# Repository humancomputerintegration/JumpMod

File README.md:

# JumpMod: Haptic Backpack that Modifies Users’ Perceived Jump

This is the repository for PCB schematics, Arduino code and hardware design files used to build the haptic backpack the "JumpMod: Haptic Backpack that Modifies Users’ Perceived Jump" paper (ACM CHI2023) by Romain Nith, Jacob Serfaty, Samuel Shatzkin, Alan Shen, and Pedro Lopes.

For more information, please refer to our paper: http://lab.plopes.org/#JumpMod

# parts for each assembly

| **Item**                                      | **Qty** | **Exemplary link**                                                                                                                                                                                                                                        | **Approx. unit cost (in USD)** |
| --------------------------------------------- | ------- | --------------------------------------------------------------------------------------------------------------------------------------------------------------------------------------------------------------------------------------------------------- | ------------------------------ |
| **Mechanical Frame**                          |
| 400mm extrusion aluminum                      | 2       | [Amazon link](https://www.amazon.com/gp/product/B08Y8N7FD1/ref=ppx_yo_dt_b_search_asin_title?ie=UTF8&psc=1)                                                                                                                                               | 4.75                           |
| 480mm extrusion aluminum                      | 1       | [Amazon link](https://www.amazon.com/Coavoo-Aluminum-Extrusion-Extruded-Profiles/dp/B0B4J6D1R6/ref=sr_1_4?crid=1TWB9FE1O3XJL&keywords=480mm+T+Slot+2020+Aluminum&qid=1670883696&s=industrial&sprefix=480mm+t+slot+2020+aluminum%2Cindustrial%2C94&sr=1-4) | 10.99                          |
| Extrusion aluminum corner bracket             | 8       | [Amazon link](https://a.co/d/40E8cxs)                                                                                                                                               | 1.10                           |
| M6 screws and nuts                            | 25      | [Amazon link](https://a.co/d/0i1jSaT)                                                                                                                                               | 1.10                           |
| Meister Backpack Straps                       | 1       | [Amazon link](https://www.amazon.com/gp/product/B077MZQ57Y/ref=ppx_yo_dt_b_search_asin_title?ie=UTF8&psc=1)                                                                                                                                               | 19.99                          |
| Hip straps                                    | 2       | [Amazon link](https://www.amazon.com/Lashing-Adjustable-Tie-Down-Motorcycle-Luggage/dp/B07JRG7LJV/ref=sr_1_8?keywords=tie+down+strap&qid=1641501015&sprefix=tie+down+str,aps,84&sr=8-8&th=1)                                                              | 5.00                           |
| Back support                                  | 2       | 3D printed                                                                                                                                                                                                                                                |                                |
| **Belt system**                               |
| 2GT-6 Timing Belt with Steel Core             | 1       | [Amazon link](https://www.amazon.com/gp/product/B07BDG8B1S/ref=ox_sc_act_title_3?smid=A2TMCEJ2C8SAEN&psc=1)                                                                                                                                               | 9.65                           |
| MGN12H 400mm Linear Rail                      | 1       | [Amazon link](https://www.amazon.com/gp/product/B07SL1HHSS/ref=ppx_yo_dt_b_search_asin_title?ie=UTF8&psc=1)                                                                                                                                               | 25.99                          |
| Micro limit switch                            | 2       | [Amazon link](https://www.amazon.com/gp/product/B07X142VGC/ref=ppx_yo_dt_b_search_asin_title?ie=UTF8&psc=1)                                                                                                                                               | 0.59                           |
| Rail limiter                                  | 2       | 3D printed                                                                                                                                                                                                                                                |                                |
| Tension system mount                          | 1       | 3D printed                                                                                                                                                                                                                                                |                                |
| Tension system encoder mount                  | 1       | 3D printed                                                                                                                                                                                                                                                |                                |
| Pololu Magnetic Encoder                       | 1       | [Pololu](https://www.pololu.com/product/3081)                                                                                                                                                                                                             | 4.45                           |
| M5 rod for encoder idle shaft                 | 1       | [Amazon link](https://www.amazon.com/gp/product/B07F3T5FKL/ref=crt_ewc_title_dp_1?ie=UTF8&psc=1&smid=AYI27JSX7SHMW)                                                                                                                                       | 0.13                           |
| Tension system pulley holder                  | 1       | 3D printed                                                                                                                                                                                                                                                |                                |
| GT2 pulley for encoder idle shaft             | 1       | [Amazon link](https://www.amazon.com/WINSINN-Aluminum-Synchronous-Timing-Printer/dp/B077GNZK3J/ref=sr_1_4?crid=3IKLQEEXLAL0O&keywords=gt2+pulley&qid=1670885253&s=industrial&sprefix=gt2+pulley%2Cindustrial%2C151&sr=1-4)                                | 1.40                           |
| 100mm guiding rods for tensioning system      | 3       | [Amazon link](https://www.amazon.com/gp/product/B01B27MJC6/ref=ppx_yo_dt_b_search_asin_title?ie=UTF8&psc=1)                                                                                                                                               | 1.49                           |
| Shaft collar for locking the rods             | 2       | [Amazon link](https://www.amazon.com/Collar-Electroplate-Ferronickel-Technology-Accessories/dp/B08BZ5XS2L/ref=sr_1_3?dchild=1&keywords=5mm+collar&qid=1628267622&sr=8-3)                                                                                  | 0.84                           |
| Bearing 5mm Bore                              | 2       | [Amazon link](https://www.amazon.com/uxcell-605-2RS-Groove-Bearings-Double/dp/B082PR238W/ref=sr_1_4?keywords=5mm+Bore+Bearing&qid=1670882058&sr=8-4)                                                                                                      | 0.95                           |
| GT2 Idler pulley                              | 1       | [Amazon link](https://www.amazon.com/WINSINN-Aluminum-Timing-Pulley-Printer/dp/B07BPGYX3G/ref=sr_1_3?keywords=gt2+bearing+5mm+bore&qid=1670885165&sprefix=gt2+bearing+5mm+b%2Caps%2C143&sr=8-3)                                                           | 1.80                           |
| Box adapter                                   | 1       | 3D printed                                                                                                                                                                                                                                                |                                |
| Box adapter’s belt clamp                      | 2       | 3D printed                                                                                                                                                                                                                                                |                                |
| **Motor & motor-driver electronics**          |
| Flipsky BLDC Motor 6374 140kv                 | 1       | [Amazon link](https://www.amazon.com/gp/product/B08G87W7WP/ref=ppx_yo_dt_b_search_asin_title?ie=UTF8&psc=1)                                                                                                                                               | 119.99                         |
| Flipsky FSESC V4.12 motor controller          | 1       | [Amazon link](https://www.amazon.com/gp/product/B07GFB55NV/ref=ppx_yo_dt_b_search_asin_title?ie=UTF8&psc=1)                                                                                                                                               | 122.99                         |
| Flipsky FSESC plate mount                     | 1       | 2D cut                                                                                                                                                                                                                                                    |                                |
| Motor GT2 pulley                              | 1       | [Amazon link](https://www.amazon.com/GT2-Aluminum-Timing-Synchronous-Printer/dp/B08DD7BWKB/ref=sr_1_2?crid=1D7YQ4O6ZEKOJ&keywords=8mm+bore+timing+pulley+gt2+black&qid=1670884591&sprefix=8mm+bore+timing+pulley+gt2+bla%2Caps%2C102&sr=8-2)              | 1.60                           |
| Motor mounting bracket                        | 1       | [Amazon link](https://www.amazon.com/gp/product/B07H8YQYGV/ref=ppx_yo_dt_b_search_asin_title?ie=UTF8&psc=1)                                                                                                                                               | 7.99                           |
| Microcontroller Seeeduino XIAO nRF52840 Sense | 1       | [Seeeduino](https://www.seeedstudio.com/Seeed-XIAO-BLE-Sense-nRF52840-p-5253.html)                                                                                                                                                                        | 15.99                          |
| **Power supply**                              |
| Battery<sup>1</sup>                           | 1       | [Amazon link](https://www.amazon.com/Lithium-Battery-20000mAh-Electric-Bicycle/dp/B08VMX8F53/ref=sr_1_21?keywords=ebike%2Bbattery&qid=1670886049&sprefix=ebike%2Bbattery%2Caps%2C194&sr=8-21&th=1)                                                        | 109.5                          |
| Battery box side panel long<sup>2</sup>       | 2       | 2D cut                                                                                                                                                                                                                                                    |                                |
| Battery box side panel short<sup>2</sup>      | 2       | 2D cut                                                                                                                                                                                                                                                    |                                |
| Battery box top/bottom panel<sup>2</sup>      | 2       | 2D cut                                                                                                                                                                                                                                                    |                                |
| Battery box corner bracket                    | 8       | 3D printed                                                                                                                                                                                                                                                |                                |
| Anti-spark power switch                       | 1       | [Amazon link](https://www.amazon.com/DIYE-Electric-Skateboard-Anti-Spark-Longboard/dp/B07MTLV55T/ref=sr_1_4?keywords=anti+spark+switch&qid=1656348713&sprefix=antispark+,aps,80&sr=8-4)                                                                   | 47.99                          |

## notes
1.	Battery cells were taken from a pre-assembled battery.
2.	2mm waterjet aluminum was used to encase the battery for all sides except the top panel, which was laser cut with 3mm acrylic.

# citing
When using or building upon this device in an academic publication, please consider citing as follows:

Romain Nith, Jacob Serfaty, Samuel G Shatzkin, Alan Shen, and Pedro Lopes. 2023. JumpMod: Haptic Backpack that Modifies Users' Perceived Jump. In Proceedings of the 2023 CHI Conference on Human Factors in Computing Systems (CHI’23), April 23–28, 2023, Hamburg, Germany. ACM, NewYork,  NY, USA, 15 pages. https://doi.org/10.1145/3544548.3580764

# contact
For any questions about this repository, please contact rnith@uchicago.edu

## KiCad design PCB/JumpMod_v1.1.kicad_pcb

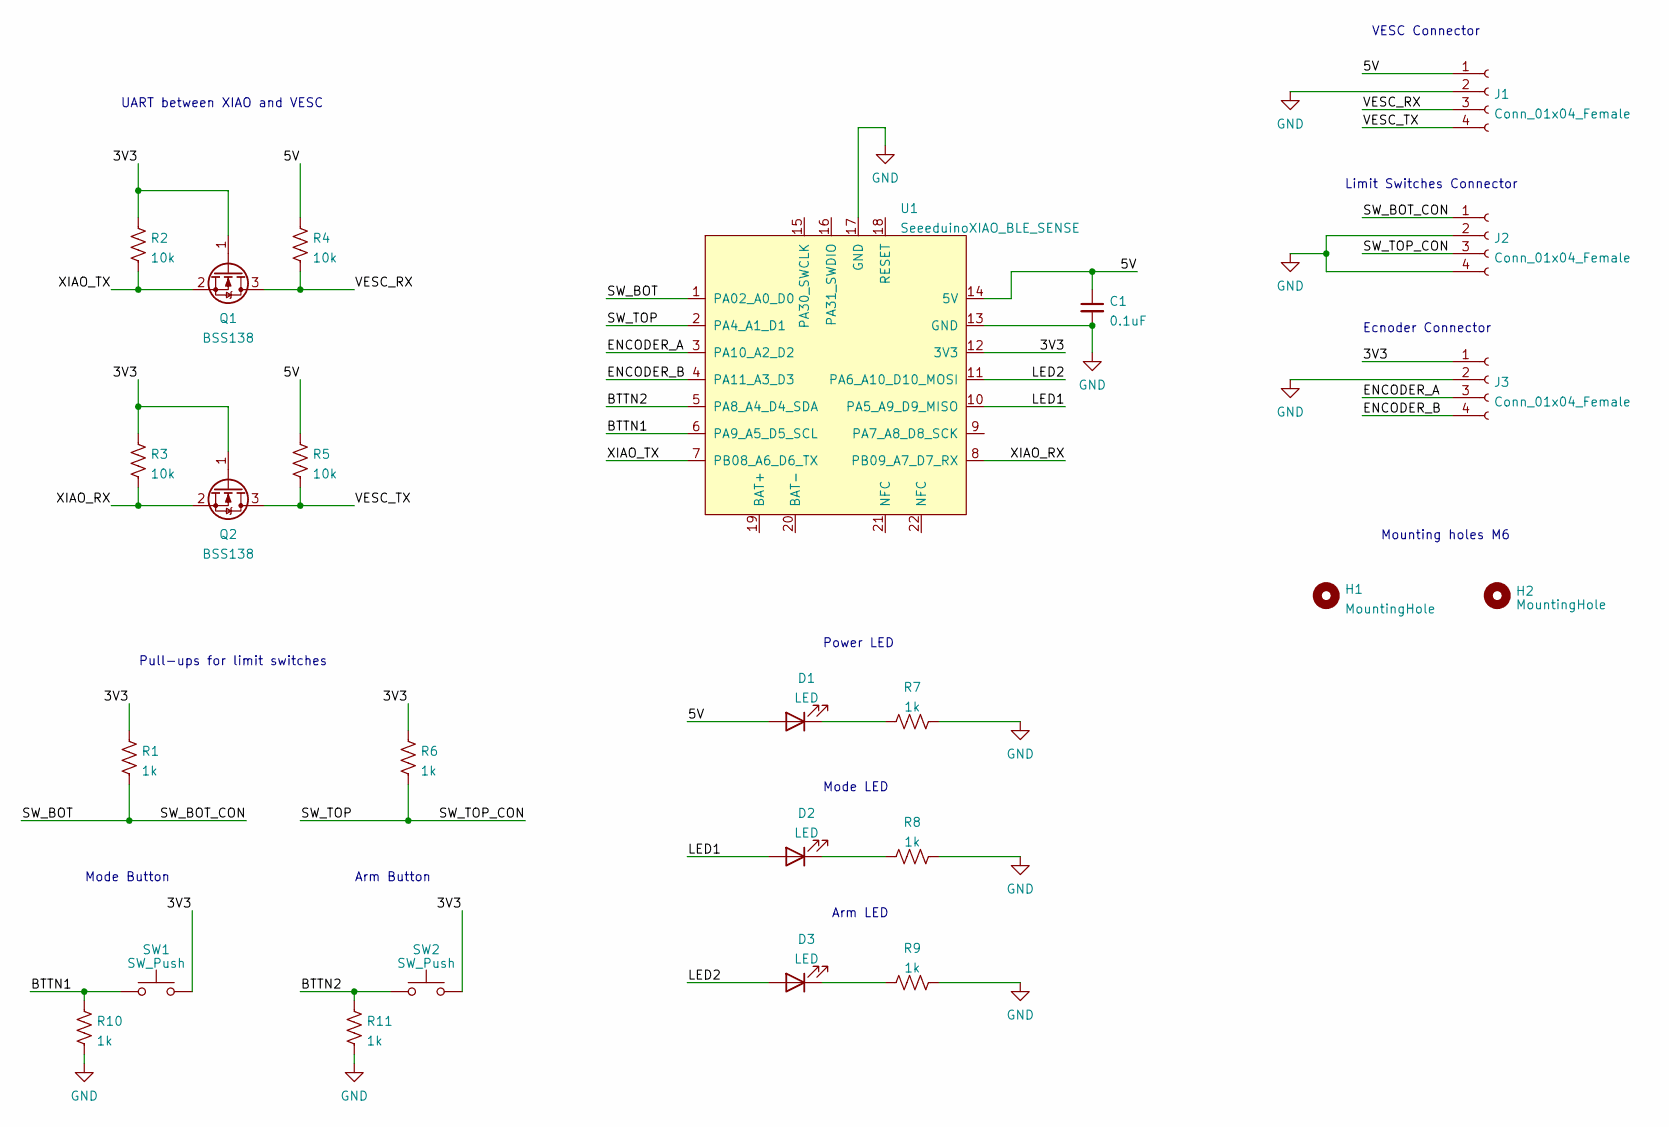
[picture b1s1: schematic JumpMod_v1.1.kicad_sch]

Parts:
C1: 0.1uF; C_0603_1608Metric
D1, D2, D3: LED; LED_0603_1608Metric
H1, H2: MountingHole; MountingHole_6.4mm_M6_Pad_Via
J1, J2, J3: Conn_01x04_Female; JST_PH_B4B-PH-K_1x04_P2.00mm_Vertical
Q1, Q2: BSS138; SOT-23
R1, R6, R7, R8, R9, R10, R11: 1k; R_0603_1608Metric
R2, R3, R4, R5: 10k; R_0603_1608Metric
SW1, SW2: SW_Push; SW_SPST_TL3305B
U1: SeeeduinoXIAO_BLE_SENSE; xiao-ble-smd

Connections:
/3V3: J3.1, Q1.1 (G), Q2.1 (G), R1.1, R2.1, R3.1, R6.1, SW1.2, SW2.2, U1.12 (3V3)
/5V: C1.1, D1.2 (A), J1.1, R4.1, R5.1, U1.14 (5V)
/BTTN1: R10.1, SW1.1, U1.6 (PA9_A5_D5_SCL)
/BTTN2: R11.1, SW2.1, U1.5 (PA8_A4_D4_SDA)
/ENCODER_A: J3.3, U1.3 (PA10_A2_D2)
/ENCODER_B: J3.4, U1.4 (PA11_A3_D3)
/LED1: D2.2 (A), U1.10 (PA5_A9_D9_MISO)
/LED2: D3.2 (A), U1.11 (PA6_A10_D10_MOSI)
/SW_BOT: J2.1, R1.2, U1.1 (PA02_A0_D0)
/SW_TOP: J2.3, R6.2, U1.2 (PA4_A1_D1)
/VESC_RX: J1.3, Q1.3 (D), R4.2
/VESC_TX: J1.4, Q2.3 (D), R5.2
/XIAO_RX: Q2.2 (S), R3.2, U1.8 (PB09_A7_D7_RX)
/XIAO_TX: Q1.2 (S), R2.2, U1.7 (PB08_A6_D6_TX)
GND: C1.2, J1.2, J2.2, J2.4, J3.2, R7.2, R8.2, R9.2, R10.2, R11.2, U1.13 (GND), U1.17 (GND)
unnamed: D1.1 (K), R7.1
unnamed: D2.1 (K), R8.1
unnamed: D3.1 (K), R9.1

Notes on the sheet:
Mounting holes M6
Mode LED
Arm Button
Mode Button
Ecnoder Connector
Power LED
VESC Connector
Limit Switches Connector
Arm LED
UART between XIAO and VESC
Pull-ups for limit switches

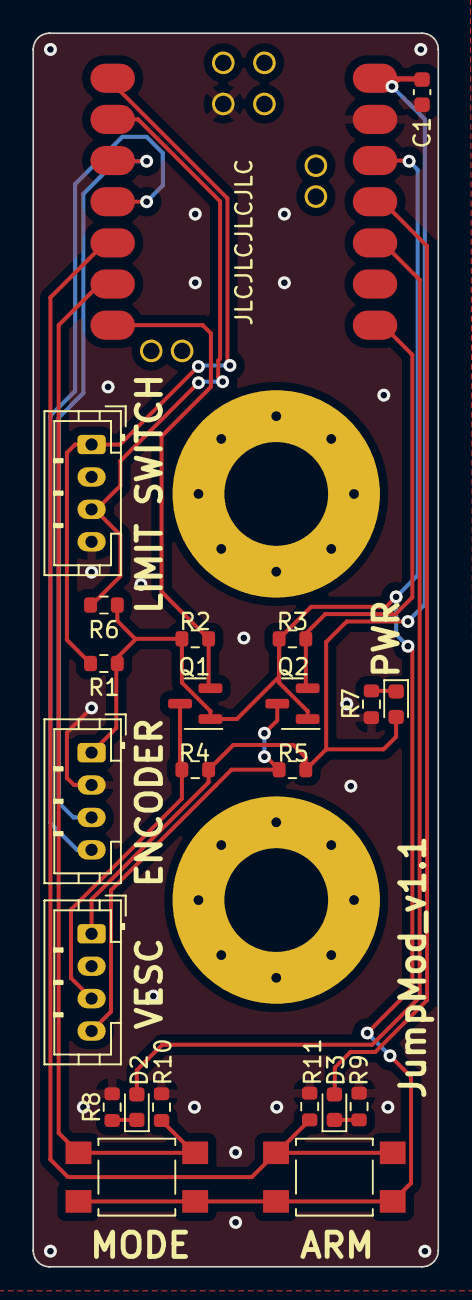
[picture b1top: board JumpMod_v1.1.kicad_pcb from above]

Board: 2 copper layers, 25.0 x 76.1 mm, 25 parts (0 on the bottom side), 18 nets.

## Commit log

2023-04-12 init repo
2023-04-12 added citation file
2024-06-03 adding images to readme and small typos
